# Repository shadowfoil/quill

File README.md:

# Quill Macropad

The "Quill" is a 3 key, 2 encoder hot-swappable macropad shield utilizing an RP2040-Zero MCU board as a controller.

vial-qmk firmware is preconfigured and ready to compile.

All PCB/Schematic files are available.

3D CAD Drawings are also available for the PCB as well as two cases that can be printed, machined, or laser cut from various materials.

Enjoy!

### Recommended PCB Specs
 - Thickness: 1.6mm PCB
 - Finish: ENIG (HASL works fine as well)
 - Soldermask: White (personal preference)
 - Silkscreen: Black (personal preference)

### PCB 

### Schematic

### Photos

### More Renders

Full Plate Style Case Exploded View

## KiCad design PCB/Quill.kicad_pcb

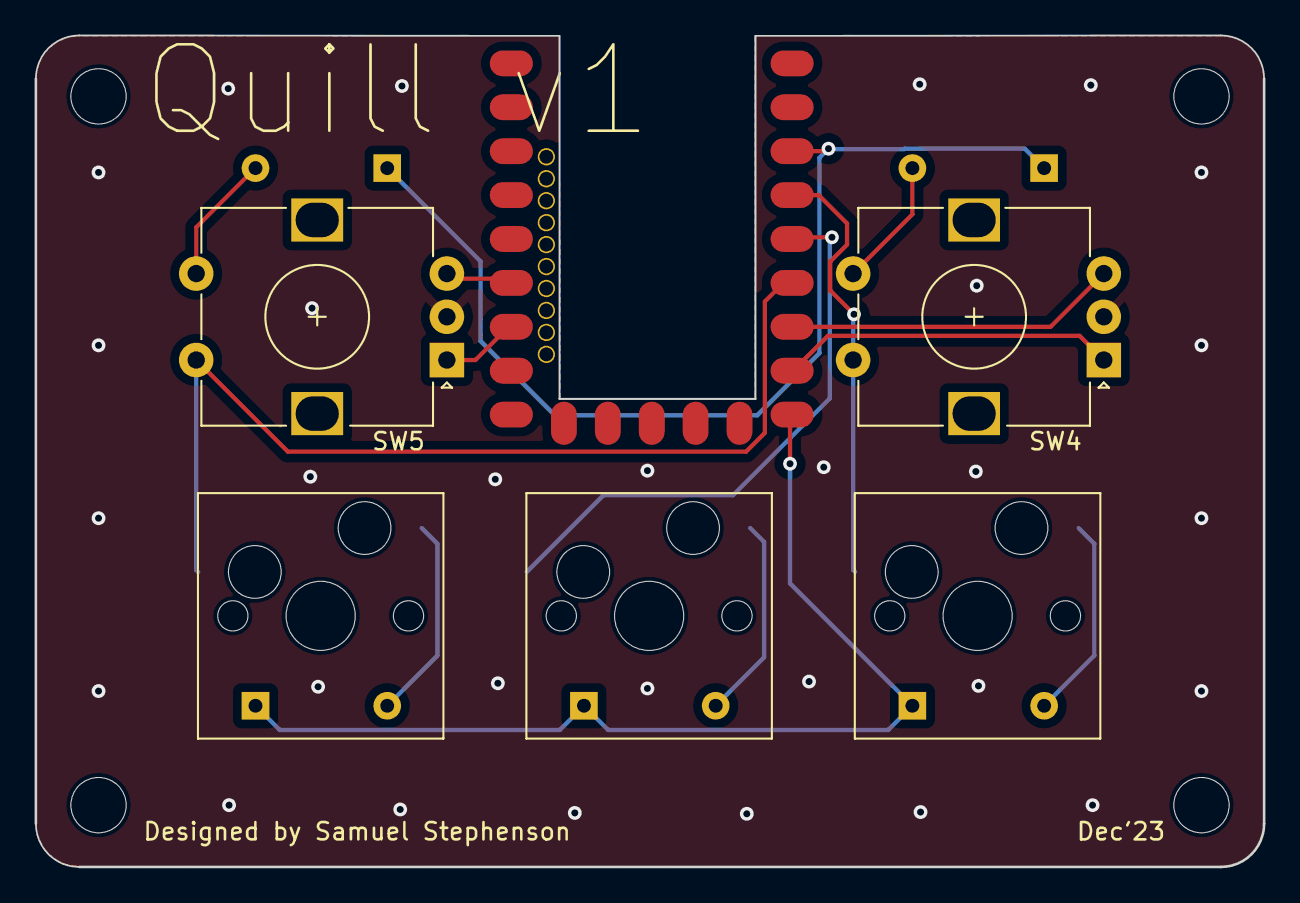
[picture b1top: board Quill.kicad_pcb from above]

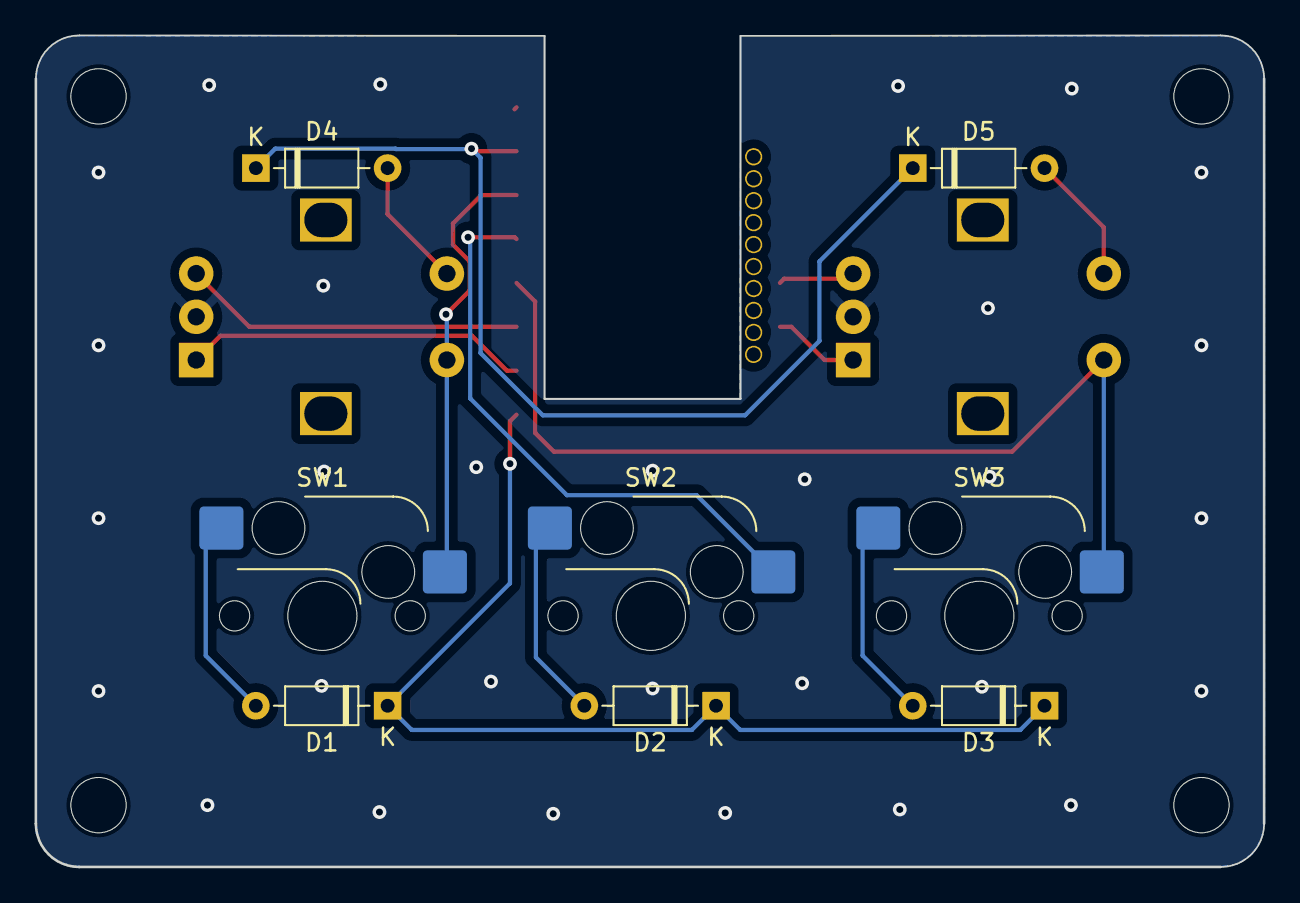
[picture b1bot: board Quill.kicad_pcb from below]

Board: 2 copper layers, 71.1 x 48.1 mm, 15 parts (8 on the bottom side), 15 nets.

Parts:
D1, D2, D3, D4, D5: 1N4148; D_DO-35_SOD27_P7.62mm_Horizontal
MH1, MH2, MH3, MH4: MountingHole_3.2mm_M3
SW1, SW2, SW3: SW_SPST; SW_Hotswap_Kailh_MX_1.00u
SW4, SW5: RotaryEncoder_Switch; RotaryEncoder_Alps_EC12E-Switch_Vertical_H20mm
U1: rp2040-zero-smd-pads

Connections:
/SW1: D1.2 (A), SW1.2 (B)
Col1: SW1.1 (A), SW4.S1, U1.3 (GP3)
Col2: SW2.1 (A), U1.4 (GP4)
Col3: SW3.1 (A), SW5.S1, U1.5 (GP5)
ENC1A: SW4.A, U1.7 (GP7)
ENC1B: SW4.B, U1.6 (GP6)
ENC2A: SW5.A, U1.17 (GP17), U1.26 (GP26)
ENC2B: SW5.B, U1.18 (GP18), U1.27 (GP27)
GND: SW4.C, SW5.C, U1.22 (GP22)
unnamed: D2.2 (A), SW2.2 (B)
unnamed: D3.2 (A), SW3.2 (B)
unnamed: D4.2 (A), SW4.S2
unnamed: D5.2 (A), SW5.S2
Row1: D1.1 (K), D2.1 (K), D3.1 (K), U1.8 (GP8)
Row2: D4.1 (K), D5.1 (K), U1.2 (GP2)

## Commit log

2023-12-28 Add all working files for quill macropad
2023-12-28 Add readme and license
